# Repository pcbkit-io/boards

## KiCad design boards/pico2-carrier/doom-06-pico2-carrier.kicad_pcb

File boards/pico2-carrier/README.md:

# 06 · pico2-carrier — the reference device as an orderable carrier

PCBKit's reference Doom device, made orderable: a carrier for the **Pimoroni Pico Plus 2**
(RP2350B, 16 MB flash, **8 MB PSRAM** on QMI chip select 1 = GPIO47; the full game's data and heap
need both, a plain Pico 2 has neither room) on the Pico's 2 × 20 sockets — with
the same 2.8" ILI9341 touch TFT (MSP2807) and ten buttons as the reference, plus a PCM5102A DAC and a
headphone jack. It runs from two 18650 Li-ion cells on its back, charged from the module's USB.
JLCPCB assembles everything but the two modules, which plug into the sockets it solders.

| | |
|---|---|
| Processor | RP2350B on the Pico Plus 2: 2 × **Cortex-M33** (ARMv8-M Mainline, DSP, single-precision FPU, TrustZone) **or** 2 × **Hazard3** (RV32IMAC + Zba/Zbb/Zbs/Zbkb/Zcb/Zcmp), chosen by the image; 150 MHz; 520 KB SRAM; 16 MB QSPI flash and 8 MB PSRAM through the QMI's 16 KB XIP cache |
| Display | 2.8" 240 × 320 ILI9341 with XPT2046 resistive touch on SPI0 (GP18 SCK, GP19 MOSI, GP16 MISO, GP17 CS, GP20 DC, GP21 RESET, GP22 backlight; touch CS GP13, IRQ GP14) |
| Input | 10 × 6 mm tact switches, as the reference: d-pad GP0–GP3, fire GP4, use GP5, strafe L/R GP6/GP7, menu GP8, enter GP9 |
| Sound | PIO I2S (GP10 BCK, GP11 LRCK, GP12 DIN) → PCM5102A (hardware mode, PLL from BCK, mute on GP15) → 470 Ω / 2.2 nF → 3.5 mm stereo jack |
| Power | 2 × 18650 Li-ion in parallel (1S2P, 3.0–4.2 V) behind reverse-cell (AO3401A) and DW01A + FS8205A protection; BQ24075 charger with power path from the module's USB; SYS → 1N5819HW → module VSYS; the module's buck-boost makes 3.3 V (up to 300 mA for the carrier) |
| Programming | the module's USB: BOOTSEL + plug → UF2 (RP2350's ROM accepts ARM and RISC-V images); SWD on the module's debug pads; the same port charges |
| Board | 160 × 100 mm, 2 layers, four M3 holes; front: display, ten buttons, charger, on/off switch, test pads; back: module (USB at the top edge), two 18650 holders, DAC, jack (right edge) |

<!-- STATUS -->
**Board status** (measured on the dev host with PCBKit's CLI): `pcbkit check`: complete — 0 errors, 0 warnings, 0 unrouted nets. 62 components, 53 nets, 504 track segments (2876 mm), 54 vias.
`analysis.run { lens: "ready" }`: Typical scenario, partly by family estimates. Nothing to fix, 1 to consider, 12 ok: weigh the warnings (tell the person about the ones that are their choice), then the board is ready to order.
`pcbkit export --format fab` succeeds without `--force`: every assembled line of the BOM has an LCSC code.
<!-- /STATUS -->

The ready lens's two notes are not faults: it estimates heat with generic package limits where the
modules' makers publish no thermal data, and reads the module's draw from its family (the board
dissipates well under 1 W). Keystone 1042 holders (C5249310) are stocked in hundreds at JLCPCB:
check before ordering more than a few boards.

## Run it in the browser

Open https://app.pcbkit.io/github/pcbkit-io/doom-handheld/tree/main/boards/pico2-carrier, open the
Laboratory and press **Run**: the page builds `doom/` for the RP2350 (with `DOOM1.WAD` linked into
flash), boots the image on a register-level model of the chip and its PSRAM, and draws the
display's frames on the board. Play with the keyboard (arrows, F fire, Space use, comma/period
strafe, M menu, Enter) or a gamepad (`input.js` maps a standard controller).

## Why it runs Doom

The Pico Plus 2's 8 MB of PSRAM is mapped at 0x1100_0000 through the XIP cache, so Doom runs as an
ordinary program: the zone heap and the screens in PSRAM, the full DOOM1.WAD in flash, on one
Hazard3 core at 150 MHz. The display takes each 320 × 200 frame as RGB565 over SPI0 at 25 MHz.

## Power

Two 18650 Li-ion cells in Keystone 1042 holders on the back, in parallel (1S2P, 3.0–4.2 V), the same
power section as `boards/rp2350-handheld`:

- **Reverse cells:** an AO3401A P-MOSFET in the plus line, its gate at the cells' minus: cells put
  in backwards leave it off and the board unpowered (it conducts both ways when they are right, so
  charging goes through it too). It cannot help one cell reversed against the other: in parallel
  they would short each other, so check both against the silkscreen's + before closing a case.
- **Protection:** DW01A + FS8205A in the pack's minus: over-charge 4.3 V, over-discharge 2.4 V,
  over-current about 3 A and short circuit, for the pack. Flat-top unprotected 18650 cells fit the
  holders.
- **Charger with power path:** a TI BQ24075 from the module's VBUS, in USB500 mode (at most 500 mA
  from the port), 800 mA fast charge (RISET 1.13 kΩ), input limit set by RILIM 1.18 kΩ, safety
  timers off (two cells in parallel charge longer than its longest timer; termination is by
  current), TS tied to 10 kΩ (no thermistor). Its output SYS runs the board from USB when one is
  plugged in and from the cells otherwise; SYS reaches the module's VSYS through a 1N5819HW
  Schottky, beside the module's own VBUS diode.
- **On/off:** the slide switch on the left edge pulls the module's 3V3_EN low (its buck-boost off;
  the charger still charges with the switch off).

| State | Current at 3.3 V (estimate) |
|---|---|
| RP2350 at 150 MHz + PSRAM | ~40 mA |
| ILI9341 2.8" with backlight | ~60–80 mA |
| PCM5102A | ~20 mA |
| **Total** | **~130 mA at 3.3 V ≈ 0.5 W with losses → ~130 mA from 3.7 V** |

Two 3000 mAh cells → **about 45 h** of play (estimate). A full charge of two empty cells at 800 mA
takes about 8 h (longer from a USB 2.0 port, which the charger limits to 500 mA).

## Charging

Plug a USB charger or computer into the module's USB. The red LED (CHG) is on while the cells
charge and goes out when they are full; the green LED (USB) is on while USB power is present. The
board runs from USB while it charges, switched on or off. Insert the cells with + at the end the
back's silkscreen marks.

## Modules plugged in by hand

The assembly solders two 1x20 female sockets and one 1x14 female socket; the modules are bought
separately and plugged in:

- **U1: Pimoroni Pico Plus 2** (PIM724, with headers): on the back, components facing the board, the USB end
  at the top edge.
- **DS1: 2.8" ILI9341 SPI TFT with touch, MSP2807** (14 pins), on the front.

## Firmware: build and flash

- `doom/` is the program: `doom_rp2350.c` is the platform layer (clocks, the PSRAM, the display on
  SPI0, the buttons, the timer), the engine is sysprog21/doom_riscv, unchanged. Pins: display SCK
  GP18, MOSI GP19, CS GP17, D/C GP20, RESET GP21, backlight GP22, the touch's CS GP13 held high;
  buttons GP0 … GP9 (up, down, left, right, fire, use, strafe left, strafe right, menu, enter).
  No console (GP0 and GP1 are buttons) and no sound yet (the DAC stays silent).
- **Build:** in PCBKit, the Laboratory's **Run** builds it (RISC-V, `DOOM1.WAD` linked into flash);
  then export the firmware (`export.run { format: "firmware" }`, or the app's export menu): `U1.uf2`.
- **Flashing on arrival:** hold the module's BOOTSEL button and plug its USB into a computer: it
  appears as the RP2350 drive; copy `U1.uf2` onto it and it reboots into the game; or
  `picotool load -x U1.uf2`. Nothing on the board to configure.

## Bill of materials

Rough cost at 10 pieces (estimates): Pimoroni Pico Plus 2 $13 · 2 × 20-pin sockets
$0.50 · ILI9341 2.8" touch module $7.00 · PCM5102A $2.00 · jack $0.60 · 10 buttons $2.90 · charger,
protection and passives $2.00 · two 18650 holders $9.80 · PCB $2.00 → **about $40** without the cells.

<!-- BOM -->
The assembly BOM as `pcbkit export --format fab` writes it (JLCPCB assembly: LCSC codes; the modules' lines are their sockets):

| Qty | Refs | Part | LCSC | Footprint |
|---|---|---|---|---|
| 2 | BT1, BT2 | 1042 | C5249310 | BatteryHolder_Keystone_1042_1x18650 |
| 5 | C1, C3, C5, C9, C12 | 100nF | C1525 | C_0402_1005Metric |
| 3 | C2, C4, C6 | 10uF | C15850 | C_0805_2012Metric |
| 2 | C7, C8 | 2.2uF | C87994 | C_0805_2012Metric |
| 2 | C10, C11 | 2.2nF | C1531 | C_0402_1005Metric |
| 1 | D1 | 1N5819HW-7-F | C82544 | D_SOD-123 |
| 1 | DS1 | Female header 1x14 2.54 mm | C2905420 | TFT_2.8in_ILI9341_Socket_1x14_P2.54mm |
| 1 | J1 | SJ1-3525N | C4991936 | Jack_3.5mm_SameSky_SJ1-352XN_Horizontal |
| 1 | Q1 | AO3401A | C15127 | SOT-23 |
| 1 | Q2 | FS8205A | C5148694 | TSSOP-8_4.4x2.93mm_P0.65mm |
| 4 | R1, R2, R3, R4 | 10kohm | C25804 | R_0603_1608Metric |
| 2 | R5, R6 | 470ohm | C25117 | R_0402_1005Metric |
| 1 | R7 | 100kohm | C25741 | R_0402_1005Metric |
| 1 | R8 | 100ohm | C25076 | R_0402_1005Metric |
| 1 | R9 | 1kohm | C11702 | R_0402_1005Metric |
| 10 | SW1, SW2, SW3, SW4, SW5, SW6, SW7, SW8, SW9, SW10 | PTS645SM43SMTR92 LFS | C221880 | SW_Tactile_SPST_6x6mm_SMD |
| 1 | SW11 | MSK12C02 | C431540 | SW_Slide_SPDT_Shouhan_MSK12C02 |
| 2 | U1 | Female header 1x20 2.54 mm | C2905423 | Raspberry_Pi_Pico_2_Socket_2x20_P2.54mm_W17.78mm |
| 1 | U2 | PCM5102APWR | C107671 | TSSOP-20_4.4x6.5mm_P0.65mm |
| 1 | U3 | DW01A | C351410 | SOT-6_1.6x2.9mm_P0.95mm |
| 1 | U4 | BQ24075RGTR | C15464 | QFN-16-1EP_3x3mm_P0.5mm_EP1.68x1.68mm |
| 2 | cBat, cSys | 4.7uF | C1779 | C_0805_2012Metric |
| 1 | cIn | 1uF | C15849 | C_0603_1608Metric |
| 1 | ledChg | red | C2286 | LED_0603_1608Metric |
| 1 | ledPg | green | C12624 | LED_0603_1608Metric |
| 2 | rChg, rPg | 1.5kohm | C25867 | R_0402_1005Metric |
| 1 | rIlim | 1.18kohm | C270651 | R_0402_1005Metric |
| 1 | rIset | 1.13kohm | C67014 | R_0402_1005Metric |
| 1 | rTs | 10kohm | C25744 | R_0402_1005Metric |
<!-- /BOM -->

## What PCBKit's engine must model to simulate it faithfully

- **Cores:** Hazard3 (RV32IMAC + the bit-manipulation and Zcb/Zcmp extensions, machine and user modes,
  PMP) — the existing RV32IMAC core plus extensions; **or** Cortex-M33 (ARMv8-M Mainline: Thumb-2 as
  for M4, FPU, stack limit registers, the security extension the SDK sets up in Secure state).
- **Interrupt controllers:** Hazard3's **Xh3irq** (an external-interrupt controller in custom CSRs:
  `meiea`, `meipa`, `meinext`… — the `Bus::csr` hook exists for exactly this) and the M33's NVIC.
- **Boot ROM:** RP2350's ROM searches flash for an IMAGE_DEF in the first 4 KB, chooses ARM or
  RISC-V, sets up XIP, handles BOOTSEL (USB UF2 + PICOBOOT) and the OTP; a model needs at least the
  image-definition parser and the XIP setup the ROM leaves behind.
- **Memory:** the **QMI** with two chip selects (flash on CS0, PSRAM on CS1/GPIO47), its timing and
  the 16 KB XIP cache; PSRAM writable through the cache.
- **Clocks:** XOSC 12 MHz, PLL_SYS 150 MHz, clk_peri, clk_hstx; the TICKS block for timers.
- **Peripherals:** PL022 SPI0 + **DMA** (the display), **PIO** (I2S), TIMER0/1, IO_BANK0/PADS with
  the RP2350's funcsel table, SIO (FIFOs, spinlocks, the RISC-V/ARM-agnostic doorbells), RESETS,
  the watchdog's scratch registers (the ROM's reboot path).
- **Board:** ILI9341 + XPT2046 models on one SPI bus with two chip selects, the PCM5102A as an I2S
  sink, and two 18650 cells as a discharge curve behind the charger's power path.

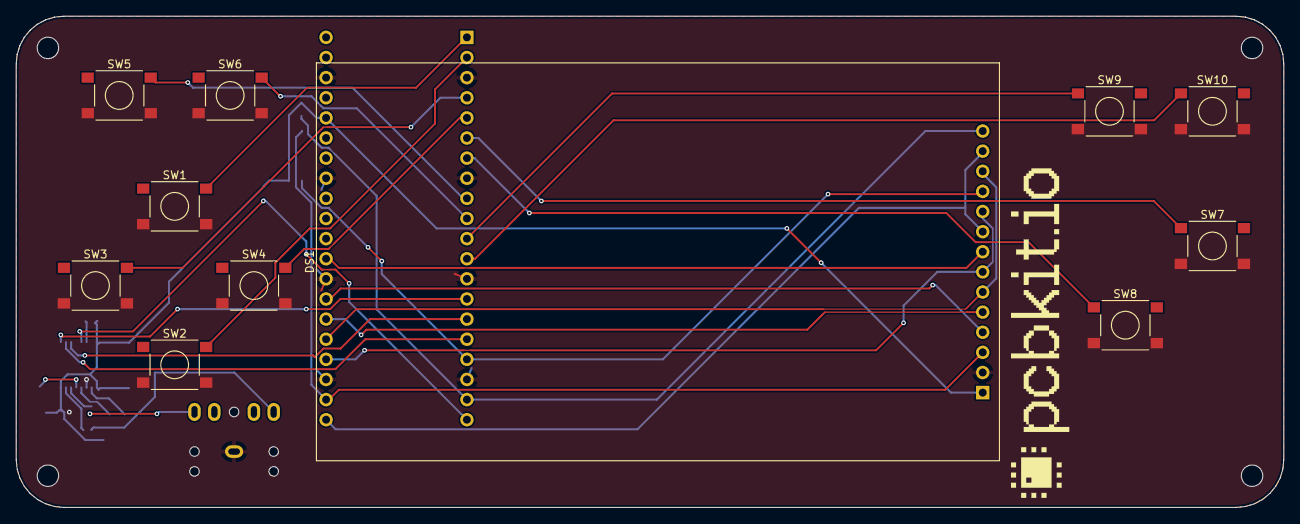
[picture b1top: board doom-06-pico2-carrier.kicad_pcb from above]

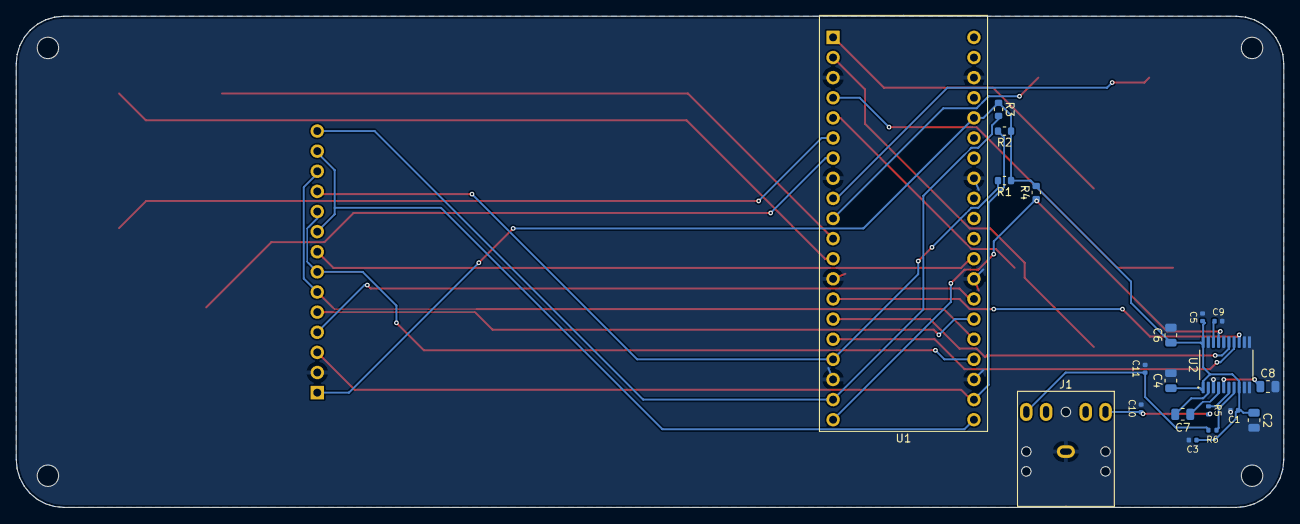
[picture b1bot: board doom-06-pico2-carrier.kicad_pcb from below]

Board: 2 copper layers, 160.0 x 62.0 mm, 36 parts (20 on the bottom side), 33 nets.

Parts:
C1, C3, C5, C9: 100nF; C_0402_1005Metric
C2, C4, C6: 10uF; C_0805_2012Metric
C7, C8: 2.2uF; C_0805_2012Metric
C10, C11: 2.2nF; C_0402_1005Metric
DS1: MSP2807 2.8in 240x320 SPI TFT module with touch (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; TFT_2.8in_ILI9341_Socket_1x14_P2.54mm
H1, H2, H3, H4: MountingHole_2.7mm_M2.5
J1: SJ1-3525N; Jack_3.5mm_SameSky_SJ1-352XN_Horizontal
R1, R2, R3, R4: 10kohm; R_0603_1608Metric
R5, R6: 470ohm; R_0402_1005Metric
SW1, SW2, SW3, SW4, SW5, SW6, SW7, SW8, SW9, SW10: PTS645SM43SMTR92 LFS; SW_Tactile_SPST_6x6mm_SMD
U1: SC1631; Raspberry_Pi_Pico_2_Socket_2x20_P2.54mm_W17.78mm
U2: PCM5102APWR; TSSOP-20_4.4x6.5mm_P0.65mm
logo: Logo_PCBKit_pcbkit.io

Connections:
DAC_MUTE: R4.1, U1.20, U2.17
DOWN: SW2.1, SW2.2, U1.2
ENTER: SW10.1, SW10.2, U1.12
FIRE: SW7.1, SW7.2, U1.6
GND: C1.2, C2.2, C3.2, C4.2, C5.2, C6.2, C8.2, C9.2, C10.2, C11.2, DS1.2, J1.1, SW1.3, SW1.4, SW2.3, SW2.4, SW3.3, SW3.4, SW4.3, SW4.4, SW5.3, SW5.4, SW6.3, SW6.4, SW7.3, SW7.4, SW8.3, SW8.4, SW9.3, SW9.4, SW10.3, SW10.4, U1.3, U1.8, U1.13, U1.18, U1.23, U1.28, U1.33, U1.38, U2.3, U2.9, U2.10, U2.11, U2.12, U2.16, U2.19
I2S_BCK: U1.14, U2.13
I2S_DIN: U1.16, U2.14
I2S_LRCK: U1.15, U2.15
LCD_BL: DS1.8, U1.29
LCD_CS: DS1.3, R2.2, U1.22
LCD_DC: DS1.5, U1.26
LCD_RST: DS1.4, U1.27
LEFT: SW3.1, SW3.2, U1.4
LINE_L: C10.1, J1.2, R5.2
LINE_R: C11.1, J1.3, R6.2
MENU: SW9.1, SW9.2, U1.11
MISO: DS1.9, DS1.13, U1.21
MOSI: DS1.6, DS1.12, U1.25
unnamed: C7.2, U2.2
unnamed: C7.1, U2.4
unnamed: C8.1, U2.5
unnamed: C9.1, U2.18
unnamed: R5.1, U2.6
unnamed: R6.1, U2.7
RIGHT: SW4.1, SW4.2, U1.5
SCK: DS1.7, DS1.10, U1.24
STRAFE_L: SW5.1, SW5.2, U1.9
STRAFE_R: SW6.1, SW6.2, U1.10
T_CS: DS1.11, R1.2, U1.17
T_IRQ: DS1.14, R3.2, U1.19
UP: SW1.1, SW1.2, U1.1
USE: SW8.1, SW8.2, U1.7
V3: C1.1, C2.1, C3.1, C4.1, C5.1, C6.1, DS1.1, R1.1, R2.1, R3.1, R4.2, U1.36, U2.1, U2.8, U2.20

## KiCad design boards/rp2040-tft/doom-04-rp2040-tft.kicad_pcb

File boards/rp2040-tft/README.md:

# 04 · rp2040-tft — the bare RP2040 with a colour screen and an SD card

Variant 02's processor without the module: the RP2040 chip with Raspberry Pi's minimal design
(12 MHz crystal, 16 MB W25Q128 QSPI flash, BOOTSEL and RESET buttons), a 1.8" colour TFT, a
microSD slot for the WAD, PWM sound through a class-D amplifier, and two 18650 Li-ion cells it
charges from its own USB-C. JLCPCB assembles everything but the display module, which plugs into
the socket it solders.

| | |
|---|---|
| Processor | RP2040 (QFN-56): 2 × **Cortex-M0+** (ARMv6-M), 133 MHz rated (rp2040-doom: 270 MHz), 264 KB SRAM, no internal flash; W25Q128JVSIQ 16 MB on the QSPI (XIP), 12 MHz crystal |
| Display | 1.8" 128 × 160 TFT, ST7735S (MSP1803), SPI0 (GPIO18 SCK, GPIO19 MOSI, GPIO17 CS, GPIO20 A0/DC, GPIO21 RESET), backlight GPIO22 |
| Storage | microSD (Hirose DM3AT) on SPI1 (GPIO10–13), card detect GPIO14 |
| Input | 8 × 6 mm tact switches: GPIO2–GPIO9 |
| Sound | GPIO15 PWM → 1 kΩ / 10 nF low-pass → PAM8403 (left channel, shutdown on GPIO16) → 8 Ω speaker on JST PH |
| Power | 2 × 18650 Li-ion in parallel (1S2P) → reverse-cell P-FET (AO3401A) → DW01A + FS8205A protection; BQ24075 charger with power path from USB-C (1 A PTC + TVS on VBUS); its SYS output feeds the TLV75533 3.3 V LDO (enabled by the slide switch) and the PAM8403 |
| Programming | USB-C to the RP2040's USB (27 Ω series, USBLC6 ESD array): hold BOOT, tap RESET → the boot ROM's UF2 drive; SWD on a 3-pin header on the back |
| Board | 132 × 104 mm, **4 layers** (GND plane on In1), four M3 holes; front: display, buttons, BOOT, RESET, on/off switch, USB-C, charge LEDs, test pads; back: the RP2040 and the rest, the two 18650 holders across the top half |

<!-- STATUS -->
**Board status** (measured on the dev host with PCBKit's CLI): `pcbkit check`: complete — 0 errors, 4 warnings (track-width-class ×2, diff-pair-uncoupled, skew), 0 unrouted nets; `issues` has 4 of 4. 92 components, 69 nets, 938 track segments (2507 mm), 123 vias.
`analysis.run { lens: "ready" }`: Typical scenario, partly by family estimates. Nothing to fix, 4 to consider, 14 ok: weigh the warnings (tell the person about the ones that are their choice), then the board is ready to order.
`pcbkit export --format fab` succeeds without `--force`: every assembled line of the BOM has an LCSC code.

| Warning | Why it stays |
|---|---|
| `diff-pair-uncoupled`, `skew` (CONN_DP / CONN_DN, ~48 mm) | USB full speed (12 Mbit/s): the connector is on the front edge, the RP2040 on the back; tens of mm uncoupled and a millimetre of skew are harmless against 4–20 ns edges |
| `track-width-class` (CONN_DP / CONN_DN necked to 0.15–0.19 mm) | short necks at the 0.4 mm pitch pads of the QFN-56 and the USB-C; signals only |
| ready lens: thermal parameters, typical scenario | estimates of the analysis, not faults of the board |
<!-- /STATUS -->

## Run it in the browser

Open https://app.pcbkit.io/github/pcbkit-io/doom-handheld/tree/main/boards/rp2040-tft, open the
Laboratory and press **Build & run**: the page builds `doom/` for the RP2040's Cortex-M0+ (with
rp2040-doom's `DOOM1.WHX` linked into the flash), boots it the way the chip's boot ROM does (the
boot2 stage checked by its CRC, then the flash in place), and draws the ST7735's frames on the
board. Play with the keyboard (arrows, F fire, Space use, M menu, Enter) or a gamepad
(`input.js`).

## Why it runs Doom

`doom/` is rp2040-doom's engine (kilograham, GPL-2, its compressed level format and its
`DOOM1.WHX`) on PCBKit's RP2040 kit instead of the Pico SDK: one core at 200 MHz (the core voltage
raised to 1.15 V first, as the SDK does above 133 MHz), the WAD read in place from the 16 MB flash,
the zone heap in the SRAM. Each 320 × 200 frame is halved (2 × 2 blocks averaged) into the panel's
middle 160 × 100, landscape, RGB565 over SPI0 at 15 MHz: 32 KB per frame, ~17 ms. The eight buttons
are read from GPIO2–9 (pulled up). The firmware does not use the microSD slot or the speaker yet:
the WAD is in the flash and the game is silent.

## Power

Two 18650 Li-ion cells in Keystone 1042 holders on the back, in parallel (1S2P, 3.0–4.2 V, about
5–7 Ah together), as on `rp2350-handheld`:

- **Reverse cells:** an AO3401A P-MOSFET in the plus line, its gate at the cells' minus: cells put
  in backwards leave it off and the board unpowered (it conducts both ways when they are right, so
  charging goes through it too). It cannot help one cell reversed against the other: in parallel
  they would short each other, so check both against the silkscreen's + before closing a case.
- **Protection:** DW01A + FS8205A in the pack's minus: over-charge 4.3 V, over-discharge 2.4 V,
  over-current about 3 A and short circuit, for the pack. Flat-top unprotected 18650 cells fit
  the holders.
- **Charger with power path:** a TI BQ24075 from the USB-C VBUS (through a 1 A PTC fuse, a 5 V TVS
  after it), in USB500 mode (at most 500 mA from the port; the CC pins' 5.1 kΩ make any Type-C
  source give 5 V), 800 mA fast charge (RISET 1.13 kΩ), input limit RILIM 1.18 kΩ, safety timers
  off (two cells charge longer than its longest timer; termination is by current), TS tied to
  10 kΩ (no thermistor). Its output SYS runs the board from USB when one is plugged in and from
  the cells otherwise.
- **Rails:** SYS (3.0–5.5 V) feeds the TLV75533 LDO (3.3 V, 500 mA; it follows the cells below about
  3.55 V, where the RP2040, the flash, the card and the display still run) and the PAM8403 directly.
  The slide switch on the left edge enables the LDO (100 kΩ holds it off); a 100 kΩ pull-down keeps
  the amplifier shut down while the RP2040 is off. The cells keep charging with the switch off.

| State | Current (estimate) |
|---|---|
| RP2040 at 270 MHz, both cores | ~50 mA |
| ST7735 with backlight | ~25 mA |
| SD card reading (bursts) | 20–60 mA |
| PAM8403 at moderate volume | 30–100 mA from SYS |
| **Typical** | **~100 mA at 3.7 V** |

Two 3000 mAh cells → **about 55 h** of play (estimate). A full charge of two empty cells at 800 mA
takes about 8 h (longer from a 500 mA USB 2.0 port).

## Charging

Plug a USB-C charger or computer into the USB-C on the bottom edge. The red LED (CHG) is on while
the cells charge and goes out when they are full; the green LED (USB) is on while USB power is
present. The board runs from USB while it charges, switched on or off. Insert both cells with +
at the end the back's silkscreen marks.

## Modules plugged in by hand

- **DS1: 1.8" 128 × 160 ST7735S SPI TFT module** (MSP1803 pinout, 8 pins: VCC, GND, CS, RESET,
  A0, SDA, SCK, LED) into the 1x8 socket JLCPCB solders on the front.
- An **8 Ω speaker** (0.5–2 W) with a JST PH 2-pin plug into J5 at the right edge of the back.
- Two **18650 cells** (the microSD card is optional: the firmware does not read it yet).

## Firmware: build and flash

- **Build:** in PCBKit, the Laboratory's **Build & run** builds `doom/` (Cortex-M0+, the kit's
  boot2 for the W25Q128 and its start-up); then export the firmware
  (`export.run { format: "firmware" }`): `U1.uf2`, the program and the WAD.
- **Flashing on arrival:** nothing to solder and no programmer, the RP2040's boot ROM has a USB
  loader. Connect the USB-C to a computer, hold **BOOT**, tap **RESET**, release BOOT (or hold BOOT
  while plugging in): the board appears as the **RPI-RP2** drive. Copy `U1.uf2` onto it; the
  RP2040 writes it into the W25Q128 and restarts into Doom. Or over SWD: the 3-pin header on the
  back (SWCLK, GND, SWDIO) takes a Raspberry Pi Debug Probe.

## Bill of materials

Rough cost at 10 pieces (estimates): RP2040 $0.80 · W25Q128 $1.00 · crystal $0.30 · ST7735 module
$3.00 · microSD socket $0.60 · PAM8403 $0.15 · BQ24075 $1.10 · DW01A + FS8205A + AO3401A $0.25 ·
TLV75533 $0.20 · USB-C + ESD + TVS + PTC $0.50 · buttons $3.00 · passives $1.00 · two 18650 holders
$9.80 · 4-layer PCB $3.00 · speaker $1.00 → **about $26** without the cells, plus assembly.

<!-- BOM -->
The assembly BOM as `pcbkit export --format fab` writes it (JLCPCB assembly: LCSC codes; the modules' lines are their sockets):

| Qty | Refs | Part | LCSC | Footprint |
|---|---|---|---|---|
| 2 | BT1, BT2 | 1042 | C5249310 | BatteryHolder_Keystone_1042_1x18650 |
| 12 | C1, C2, C3, C4, C5, C9, C12, C13, C14, C15, C18, C19 | 100nF | C1525 | C_0402_1005Metric |
| 1 | C6 | 10uF | C19702 | C_0603_1608Metric |
| 1 | C7 | 10nF | C15195 | C_0402_1005Metric |
| 6 | C10, C11, C24, C25, C26, C28 | 1uF | C52923 | C_0402_1005Metric |
| 2 | C16, C17 | 15pF | C1548 | C_0402_1005Metric |
| 3 | C22, C23, cIn | 1uF | C15849 | C_0603_1608Metric |
| 1 | C27 | 22uF | C12891 | C_1206_3216Metric |
| 1 | C29 | 470nF | C47339 | C_0402_1005Metric |
| 1 | D1 | tvs 5V | C918844 | D_SOD-323 |
| 1 | DS1 | Female header 1x8 2.54 mm | C2905417 | TFT_1.8in_ST7735_Socket_1x08_P2.54mm |
| 1 | F1 | PTC 1000mA | C20800 | Fuse_1206_3216Metric |
| 1 | J1 | USB_C_Receptacle_USB2.0_16P | C165948 | USB_C_Receptacle_USB2.0_16P |
| 1 | J3 | PinHeader_1x03_P2.54mm_Vertical | C49257 | PinHeader_1x03_P2.54mm_Vertical |
| 1 | J4 | DM3AT-SF-PEJM5 | C114218 | Hirose_DM3AT_microSD_socket_push-push |
| 1 | J5 | S2B-PH-K-S(LF)(SN) | C173752 | JST_PH_S2B-PH-K_1x02_P2.00mm_Horizontal |
| 1 | Q1 | AO3401A | C15127 | SOT-23 |
| 1 | Q2 | FS8205A | C5148694 | TSSOP-8_4.4x2.93mm_P0.65mm |
| 4 | R1, R10, R17, rBoot | 1kohm | C11702 | R_0402_1005Metric |
| 2 | R2, R3 | 27ohm | C25100 | R_0402_1005Metric |
| 6 | R4, R6, R7, R8, R9, rTs | 10kohm | C25744 | R_0402_1005Metric |
| 3 | R11, R12, R15 | 100kohm | C25741 | R_0402_1005Metric |
| 2 | R13, R14 | 5.1kohm | C25905 | R_0402_1005Metric |
| 1 | R16 | 100ohm | C25076 | R_0402_1005Metric |
| 10 | SW1, SW2, SW3, SW4, SW5, SW6, SW7, SW8, boot, reset | PTS645SM43SMTR92 LFS | C221880 | SW_Tactile_SPST_6x6mm_SMD |
| 1 | SW9 | MSK12C02 | C431540 | SW_Slide_SPDT_Shouhan_MSK12C02 |
| 1 | U1 | RP2040 | C2040 | QFN-56-1EP_7x7mm_P0.4mm_EP3.1x3.1mm |
| 1 | U2 | DW01A | C351410 | SOT-6_1.6x2.9mm_P0.95mm |
| 1 | U3 | W25Q128JVSIQ | C97521 | SOIC-8_5.23x5.28mm_P1.27mm |
| 1 | U4 | TLV75533PDBVR | C404027 | SOT-23-5 |
| 1 | U5 | PAM8403DR | C5122557 | SOIC-16_3.9x9.9mm_P1.27mm |
| 1 | U6 | BQ24075RGTR | C15464 | QFN-16-1EP_3x3mm_P0.5mm_EP1.68x1.68mm |
| 1 | U7 | ESD 2-line | C7519 | SOT-23-6 |
| 1 | Y1 | 12MHz 10pF | C20625731 | Crystal_SMD_3225-4Pin |
| 2 | cBat, cSys | 4.7uF | C1779 | C_0805_2012Metric |
| 1 | ledChg | red | C2286 | LED_0603_1608Metric |
| 1 | ledPg | green | C12624 | LED_0603_1608Metric |
| 2 | rChg, rPg | 1.5kohm | C25867 | R_0402_1005Metric |
| 1 | rIlim | 1.18kohm | C270651 | R_0402_1005Metric |
| 1 | rIset | 1.13kohm | C67014 | R_0402_1005Metric |
<!-- /BOM -->

## What PCBKit's engine must model to simulate it faithfully

Everything of variant 02, plus: the boot ROM's **USB mass-storage UF2 loader** if flashing is to be
simulated; the **SSI/XIP with 16 MB** (the current SoC maps 2 MB); **two PL022 SPI** blocks with
**DMA** (paced by the SPI's DREQ); the **PWM slice** as an audio source (duty → sample); an SD card
model in SPI mode (CMD0/8/55/41/58/17/18/24, a FAT image as its contents); an ST7735 model; the
BQ24075/DW01A/LDO power chain as a two-cell battery model with protection thresholds, the power
path and the charge current.

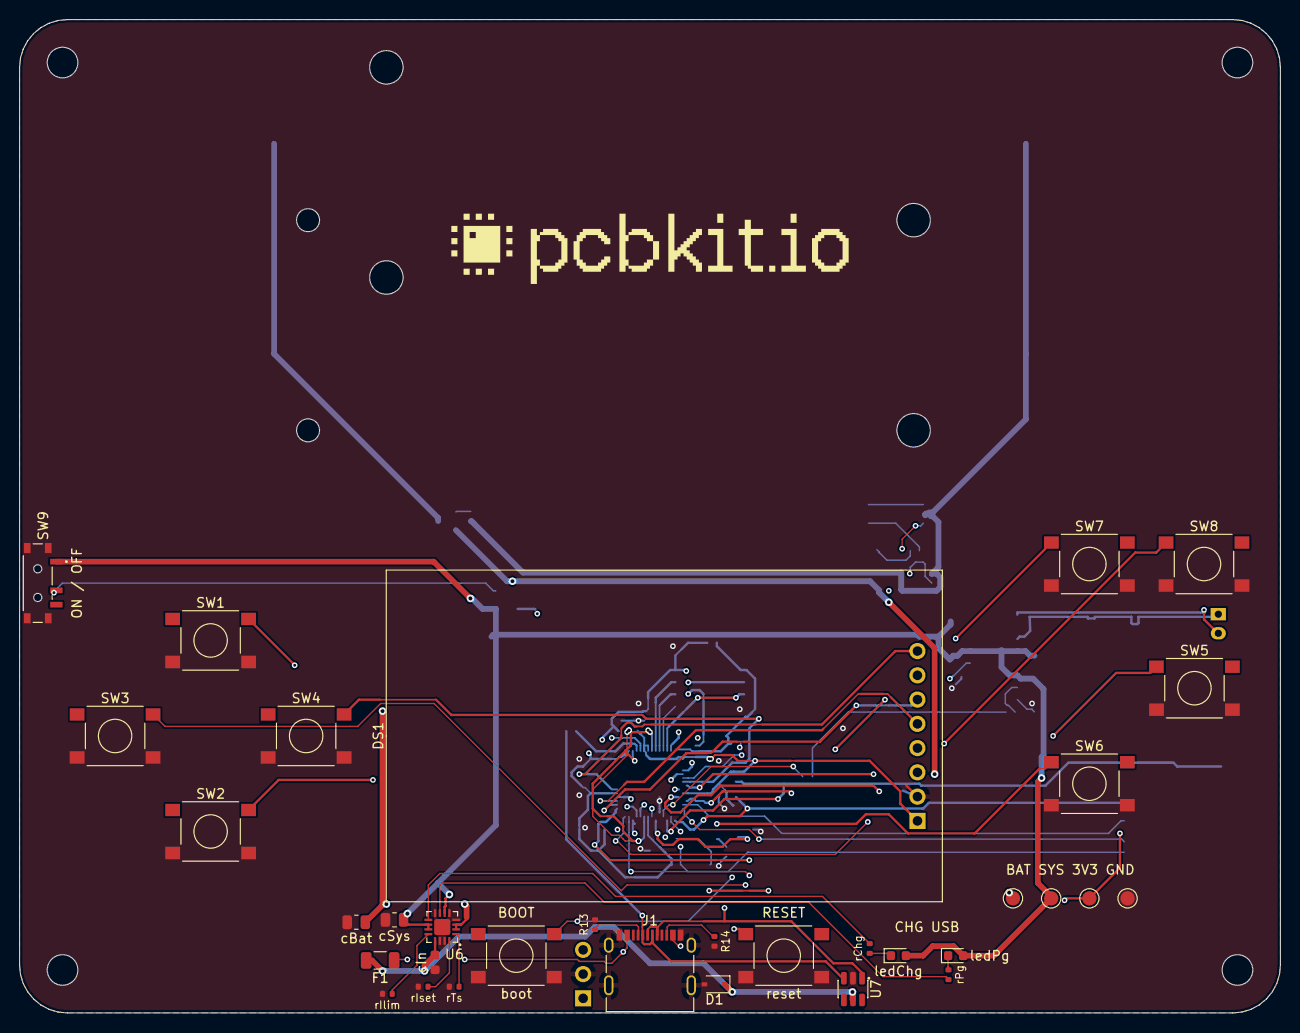
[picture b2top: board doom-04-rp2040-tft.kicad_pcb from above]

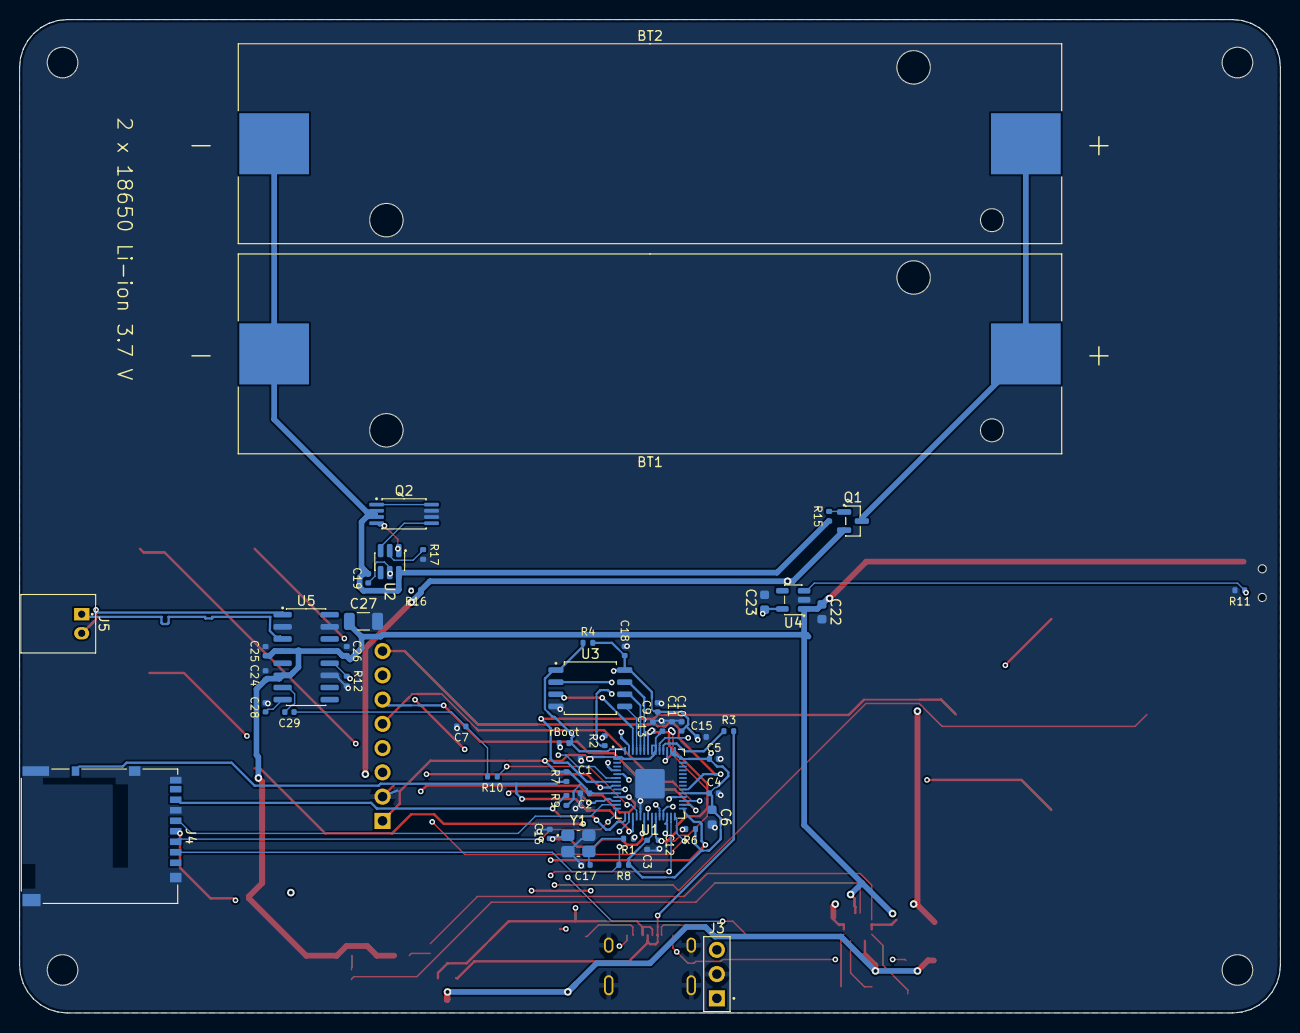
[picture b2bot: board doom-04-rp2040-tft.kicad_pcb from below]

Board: 4 copper layers, 132.0 x 104.0 mm, 92 parts (54 on the bottom side), 68 nets.

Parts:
BT1, BT2: 1042; BatteryHolder_Keystone_1042_1x18650
C1, C2, C3, C4, C5, C9, C12, C13, C14, C15, C18, C19: 100nF; C_0402_1005Metric
C6: 10uF; C_0603_1608Metric
C7: 10nF; C_0402_1005Metric
C10, C11, C24, C25, C26, C28: 1uF; C_0402_1005Metric
C16, C17: 15pF; C_0402_1005Metric
C22, C23: 1uF; C_0603_1608Metric
C27: 22uF; C_1206_3216Metric
C29: 470nF; C_0402_1005Metric
D1: tvs 5V; D_SOD-323
DS1: MSP1803 1.8in 128x160 SPI TFT module (ST7735S); TFT_1.8in_ST7735_Socket_1x08_P2.54mm
F1: PTC 1000mA; Fuse_1206_3216Metric
H1, H2, H3, H4: MountingHole_3.2mm_M3
J1: USB_C_Receptacle_USB2.0_16P
J3: PinHeader_1x03_P2.54mm_Vertical
J4: DM3AT-SF-PEJM5; Hirose_DM3AT_microSD_socket_push-push
J5: S2B-PH-K-S(LF)(SN); JST_PH_S2B-PH-K_1x02_P2.00mm_Horizontal
Q1: AO3401A; SOT-23
Q2: FS8205A; TSSOP-8_4.4x2.93mm_P0.65mm
R1, R10, R17: 1kohm; R_0402_1005Metric
R2, R3: 27ohm; R_0402_1005Metric
R4, R6, R7, R8, R9: 10kohm; R_0402_1005Metric
R11, R12, R15: 100kohm; R_0402_1005Metric
R13, R14: 5.1kohm; R_0402_1005Metric
R16: 100ohm; R_0402_1005Metric
SW1, SW2, SW3, SW4, SW5, SW6, SW7, SW8: PTS645SM43SMTR92 LFS; SW_Tactile_SPST_6x6mm_SMD
SW9: MSK12C02; SW_Slide_SPDT_Shouhan_MSK12C02
U1: RP2040; QFN-56-1EP_7x7mm_P0.4mm_EP3.1x3.1mm
U2: DW01A; SOT-6_1.6x2.9mm_P0.95mm
U3: W25Q128JVSIQ; SOIC-8_5.23x5.28mm_P1.27mm
U4: TLV75533PDBVR; SOT-23-5
U5: PAM8403DR; SOIC-16_3.9x9.9mm_P1.27mm
U6: BQ24075RGTR; QFN-16-1EP_3x3mm_P0.5mm_EP1.68x1.68mm
U7: ESD 2-line; SOT-23-6
Y1: 12MHz 10pF; Crystal_SMD_3225-4Pin
boot: PTS645SM43SMTR92 LFS; SW_Tactile_SPST_6x6mm_SMD
cBat: 4.7uF; C_0805_2012Metric
cIn: 1uF; C_0603_1608Metric
cSys: 4.7uF; C_0805_2012Metric
ledChg: red; LED_0603_1608Metric
ledPg: green; LED_0603_1608Metric
logo: Logo_PCBKit_pcbkit.io
rBoot: 1kohm; R_0402_1005Metric
rChg: 1.5kohm; R_0402_1005Metric
rIlim: 1.18kohm; R_0402_1005Metric
rIset: 1.13kohm; R_0402_1005Metric
rPg: 1.5kohm; R_0402_1005Metric
rTs: 10kohm; R_0402_1005Metric
reset: PTS645SM43SMTR92 LFS; SW_Tactile_SPST_6x6mm_SMD
tpBat: TestPoint_Round_D1.5mm
tpGnd: TestPoint_Round_D1.5mm
tpSys: TestPoint_Round_D1.5mm
tpV3: TestPoint_Round_D1.5mm

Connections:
AMP_SD: R12.1, U1.27, U5.12
AUDIO: C7.1, C29.1, R10.2
BAT: Q1.2, R16.1, U6.2, U6.3, cBat.1, tpBat.1
BAT_IN: BT1.2, BT2.2, Q1.3
BOOTSEL: boot.1, boot.2, rBoot.1
CELL_N: BT1.1, BT2.1, C19.2, Q2.2, Q2.3, R15.1, U2.6
CHG_LED: ledChg.1, rChg.1
CHG_N: U6.9, rChg.2
CONN_DN: J1.A7, J1.B7, R3.2, U7.3
CONN_DP: J1.A6, J1.B6, R2.2, U7.1
DOWN: SW2.1, SW2.2, U1.5
DVDD: C11.1, C12.1, C13.1, U1.23, U1.45, U1.50
FIRE: SW5.1, SW5.2, U1.8
GND: C1.2, C2.2, C3.2, C4.2, C5.2, C6.2, C7.2, C9.2, C10.2, C11.2, C12.2, C13.2, C14.2, C15.2, C16.2, C17.2, C18.2, C22.2, C23.2, C24.2, C25.2, C26.2, C27.2, C28.2, D1.2, DS1.2, J1.A1, J1.B1, J1.S1, J3.2, J4.6, J4.10, J4.SH, Q2.6, Q2.7, R11.2, R12.2, R13.2, R14.2, R17.2, SW1.3, SW1.4, SW2.3, SW2.4, SW3.3, SW3.4, SW4.3, SW4.4, SW5.3, SW5.4, SW6.3, SW6.4, SW7.3, SW7.4, SW8.3, SW8.4, SW9.4, U1.19, U1.57, U3.4, U4.2, U5.2, U5.11, U5.15, U6.4, U6.5, U6.8, U6.14, U6.15, U6.17, U7.2, Y1.2, Y1.4, boot.3, boot.4, cBat.2, cIn.2, cSys.2, rIlim.2, rIset.2, rTs.2, reset.3, reset.4, tpGnd.1
ILIM: U6.12, rIlim.1
ISET: U6.16, rIset.1
LCD_BL: DS1.8, U1.34
LCD_CS: DS1.3, U1.28
LCD_DC: DS1.5, U1.31
LCD_RST: DS1.4, U1.32
LDO_EN: R11.1, SW9.2, U4.3
LEFT: SW3.1, SW3.2, U1.6
MOSI: DS1.6, U1.30
unnamed: C16.1, U1.20, Y1.1
unnamed: C19.1, R16.2, U2.5
unnamed: C28.1, U5.8
unnamed: C29.2, U5.7
unnamed: Q2.4, U2.1
unnamed: Q2.5, U2.3
unnamed: R1.1, U1.21
unnamed: R2.1, U1.47
unnamed: R3.1, U1.46
unnamed: R4.1, U1.56, U3.1, rBoot.2
unnamed: R17.1, U2.2
unnamed: U1.51, U3.7
unnamed: U1.52, U3.6
unnamed: U1.53, U3.5
unnamed: U1.54, U3.3
unnamed: U1.55, U3.2
PG_LED: ledPg.1, rPg.1
PG_N: U6.7, rPg.2
PWM_L: R10.1, U1.18
RIGHT: SW4.1, SW4.2, U1.7
RUN: R6.2, U1.26, reset.1, reset.2
SCK: DS1.7, U1.29
SD_CD: J4.9, R7.1, U1.17
SD_CS: J4.2, R8.2, U1.16
SD_MISO: J4.7, R9.2, U1.15
SD_MOSI: J4.3, U1.14
SD_SCK: J4.5, U1.13
SELECT: SW7.1, SW7.2, U1.12
SPK_N: J5.1, U5.3
SPK_P: J5.2, U5.1
START: SW8.1, SW8.2, U1.11
SWCLK: J3.1, U1.24
SWDIO: J3.3, U1.25
SYS: C22.1, C24.1, C25.1, C26.1, C27.1, SW9.1, U4.1, U5.4, U5.6, U5.13, U6.6, U6.10, U6.11, cSys.1, ledChg.2, ledPg.2, tpSys.1
TS: U6.1, rTs.1
U1Support/XO: C17.1, R1.2, Y1.3
U2Support/DRAIN: Q2.1, Q2.8
UP: SW1.1, SW1.2, U1.4
USE: SW6.1, SW6.2, U1.9
V3: C1.1, C2.1, C3.1, C4.1, C5.1, C6.1, C9.1, C10.1, C14.1, C15.1, C18.1, C23.1, DS1.1, J4.4, R4.2, R6.1, R7.2, R8.1, R9.1, U1.1, U1.10, U1.22, U1.33, U1.42, U1.43, U1.44, U1.48, U1.49, U3.8, U4.5, tpV3.1
VBUS: D1.1, F1.2, U6.13, U7.5, cIn.1
reversed/gate: Q1.1, R15.2
usb/power/cc1: J1.A5, R13.1
usb/power/cc2: J1.B5, R14.1
usb/power/raw: F1.1, J1.A4, J1.B4

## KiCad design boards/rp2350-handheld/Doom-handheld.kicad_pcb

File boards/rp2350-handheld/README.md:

# RP2350 Doom handheld

A carrier board for a **Pimoroni Pico Plus 2** (RP2350B with 16 MB of flash and 8 MB of PSRAM)
under a **2.8" ILI9341 SPI TFT module** (the MSP2807, with touch), with a d-pad, strafe, fire, use,
menu and enter buttons. Power and flashing go through the Pico's USB-C. The outline is a red
keycard with a lanyard slot; the wordmark on the silkscreen is our own drawing.

## Run it in the browser

Open https://app.pcbkit.io/github/pcbkit-io/doom-handheld/tree/main/boards/rp2350-handheld, open
the Laboratory and press **Run**: the page builds `doom/` for the RP2350 (with `DOOM1.WAD` linked
into flash), boots the image on a register-level model of the chip and its PSRAM, and draws the
ILI9341's frames on the board. Play with the keyboard (arrows, F fire, Space use, comma/period
strafe, M menu, Enter) or a gamepad (`input.js` maps a standard controller).

## Parts

| Ref | Part | Note |
|---|---|---|
| U1 | Pimoroni Pico Plus 2 (PIM722) | on the back, on two 1x20 headers |
| lcd | 2.8" ILI9341 SPI TFT with touch (MSP2807) | on a 1x14 female header; the touch shares SPI0 and stays deselected |
| up, down, left, right, strafeLeft, strafeRight, fire, use, menu, enter | 6 x 6 mm tactile switch | to ground; the RP2350's pull-ups |
| J1 | 1x3 2.54 mm header | the console: UART0 at 115200 baud (TX, RX, GND) |

## Pins

| Signal | GPIO |
|---|---|
| Display SCK, MOSI (SPI0) | GP18, GP19 |
| Display CS, D/C, RESET, backlight | GP17, GP20, GP21, GP22 |
| Up, down, left, right, fire, use, strafe left, strafe right, menu, enter | GP2 … GP11 |
| Console TX, RX (UART0) | GP0, GP1 |
| PSRAM chip select | GP47 (on the Pico Plus 2) |

## The firmware

`doom/doom_rp2350.c` is the platform layer: clocks (12 MHz crystal, 150 MHz from the PLL), the
PSRAM on the QSPI interface, the display over SPI0 at 25 MHz, the buttons, the timer. The engine
in `doom/` is sysprog21/doom_riscv, unchanged. The program runs on the RP2350's RISC-V (Hazard3)
cores from flash; the zone heap and the screens are in PSRAM. There is no sound.

The simulation runs one instruction per clock and does not charge flash or PSRAM latency, so the
board itself may draw fewer frames per second than the browser shows.

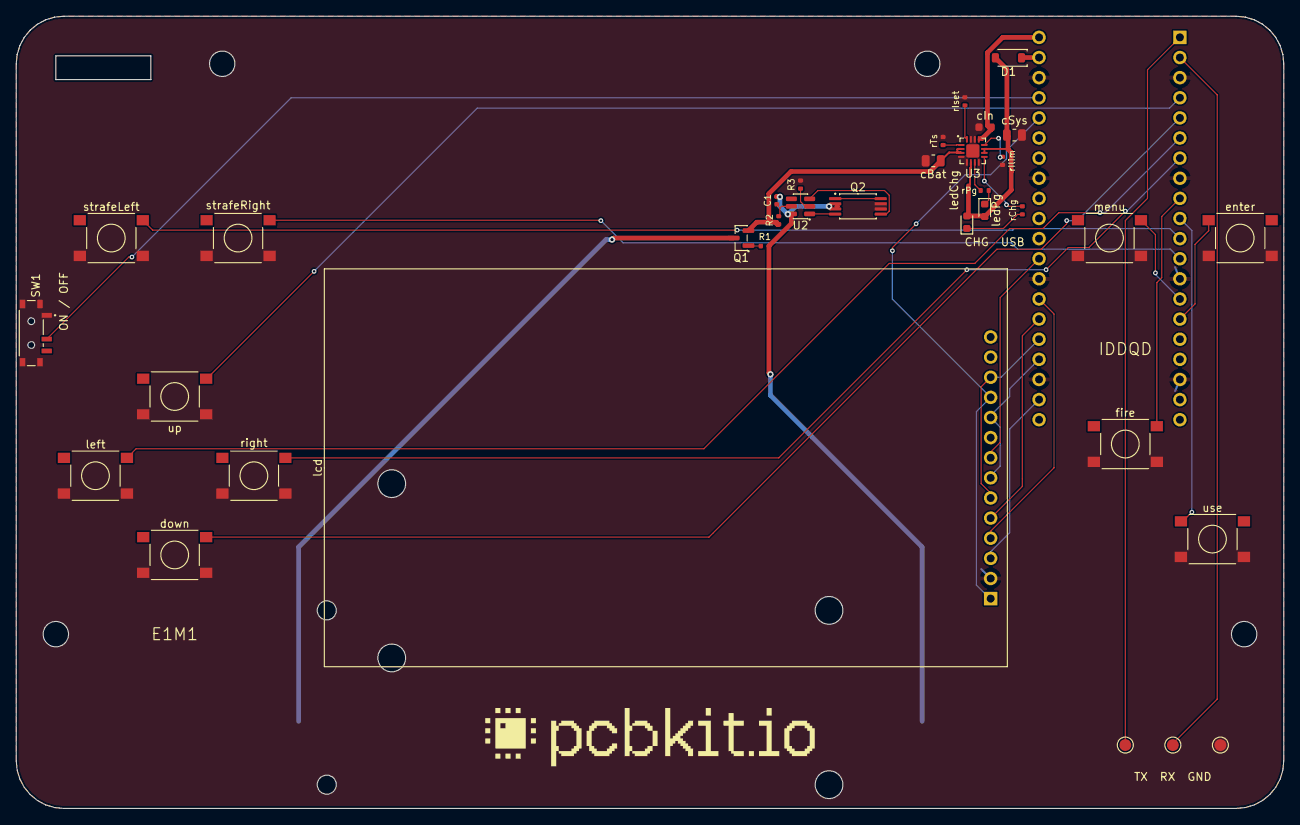
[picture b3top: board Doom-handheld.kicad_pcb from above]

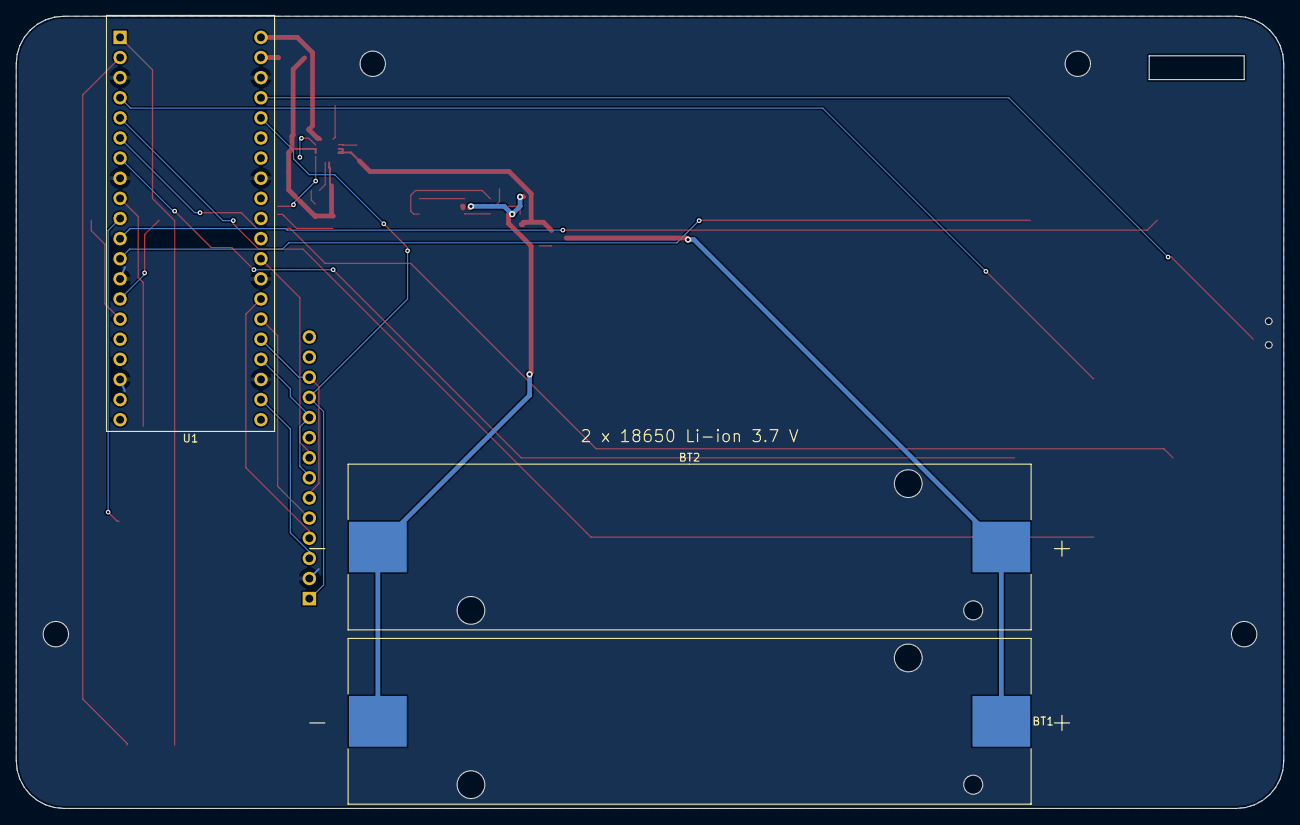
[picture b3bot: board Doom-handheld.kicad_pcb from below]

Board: 2 copper layers, 160.0 x 100.0 mm, 42 parts (3 on the bottom side), 40 nets.

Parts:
BT1, BT2: 1042; BatteryHolder_Keystone_1042_1x18650
C1: 100nF; C_0402_1005Metric
D1: 1N5819HW-7-F; D_SOD-123
H1, H2, H3, H4: MountingHole_3.2mm_M3
Q1: AO3401A; SOT-23
Q2: FS8205A; TSSOP-8_4.4x2.93mm_P0.65mm
R1: 100kohm; R_0402_1005Metric
R2: 100ohm; R_0402_1005Metric
R3: 1kohm; R_0402_1005Metric
SW1: MSK12C02; SW_Slide_SPDT_Shouhan_MSK12C02
U1: PIM724; Pimoroni_Pico_Plus_2_Socket_2x20_P2.54mm_W17.78mm
U2: DW01A; SOT-6_1.6x2.9mm_P0.95mm
U3: BQ24075RGTR; QFN-16-1EP_3x3mm_P0.5mm_EP1.68x1.68mm
cBat: 4.7uF; C_0805_2012Metric
cIn: 1uF; C_0603_1608Metric
cSys: 4.7uF; C_0805_2012Metric
down: PTS645SM43SMTR92 LFS; SW_Tactile_SPST_6x6mm_SMD
enter: PTS645SM43SMTR92 LFS; SW_Tactile_SPST_6x6mm_SMD
fire: PTS645SM43SMTR92 LFS; SW_Tactile_SPST_6x6mm_SMD
lcd: MSP2807 2.8in 240x320 SPI TFT module with touch (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; TFT_2.8in_ILI9341_Socket_1x14_P2.54mm
ledChg: red; LED_0603_1608Metric
ledPg: green; LED_0603_1608Metric
left: PTS645SM43SMTR92 LFS; SW_Tactile_SPST_6x6mm_SMD
logo: Logo_PCBKit_pcbkit.io
menu: PTS645SM43SMTR92 LFS; SW_Tactile_SPST_6x6mm_SMD
rChg: 1.5kohm; R_0402_1005Metric
rIlim: 1.18kohm; R_0402_1005Metric
rIset: 1.13kohm; R_0402_1005Metric
rPg: 1.5kohm; R_0402_1005Metric
rTs: 10kohm; R_0402_1005Metric
right: PTS645SM43SMTR92 LFS; SW_Tactile_SPST_6x6mm_SMD
strafeLeft: PTS645SM43SMTR92 LFS; SW_Tactile_SPST_6x6mm_SMD
strafeRight: PTS645SM43SMTR92 LFS; SW_Tactile_SPST_6x6mm_SMD
tpGnd: TestPoint_Round_D1.5mm
tpRx: TestPoint_Round_D1.5mm
tpTx: TestPoint_Round_D1.5mm
up: PTS645SM43SMTR92 LFS; SW_Tactile_SPST_6x6mm_SMD
use: PTS645SM43SMTR92 LFS; SW_Tactile_SPST_6x6mm_SMD

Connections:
BAT: Q1.2, R2.1, U3.2, U3.3, cBat.1
BAT_IN: BT1.2, BT2.2, Q1.3
CELL_N: BT1.1, BT2.1, C1.2, Q2.2, Q2.3, R1.2, U2.6
CHG_LED: ledChg.1, rChg.1
CHG_N: U3.9, rChg.2
DOWN: U1.5, down.1, down.2
ENTER: U1.15, enter.1, enter.2
FIRE: U1.9, fire.1, fire.2
GND: Q2.6, Q2.7, R3.2, SW1.1, SW1.4, U1.3, U1.8, U1.13, U1.18, U1.23, U1.28, U1.33, U1.38, U3.4, U3.5, U3.8, U3.14, U3.15, U3.17, cBat.2, cIn.2, cSys.2, down.3, down.4, enter.3, enter.4, fire.3, fire.4, lcd.2, left.3, left.4, menu.3, menu.4, rIlim.2, rIset.2, rTs.2, right.3, right.4, strafeLeft.3, strafeLeft.4, strafeRight.3, strafeRight.4, tpGnd.1, up.3, up.4, use.3, use.4
ILIM: U3.12, rIlim.1
ISET: U3.16, rIset.1
LCD_CS: U1.22, lcd.3
LCD_DC: U1.26, lcd.5
LCD_LED: U1.29, lcd.8
LCD_MOSI: U1.25, lcd.6, lcd.12
LCD_RESET: U1.27, lcd.4
LCD_SCK: U1.24, lcd.7, lcd.10
LEFT: U1.6, left.1, left.2
MENU: U1.14, menu.1, menu.2
unnamed: C1.1, R2.2, U2.5
unnamed: Q2.4, U2.1
unnamed: Q2.5, U2.3
unnamed: R3.1, U2.2
PG_LED: ledPg.1, rPg.2
PG_N: U3.7, rPg.1
PWR_EN: SW1.2, U1.37
RIGHT: U1.7, right.1, right.2
RX: U1.2, tpRx.1
STRAFE_L: U1.11, strafeLeft.1, strafeLeft.2
STRAFE_R: U1.12, strafeRight.1, strafeRight.2
SYS: D1.2, U3.6, U3.10, U3.11, cSys.1, ledChg.2, ledPg.2
TS: U3.1, rTs.1
TX: U1.1, tpTx.1
U2Support/DRAIN: Q2.1, Q2.8
UP: U1.4, up.1, up.2
USE: U1.10, use.1, use.2
V3: U1.36, lcd.1, lcd.11
VBUS: U1.40, U3.13, cIn.1
VSYS: D1.1, U1.39
reversed/gate: Q1.1, R1.1
